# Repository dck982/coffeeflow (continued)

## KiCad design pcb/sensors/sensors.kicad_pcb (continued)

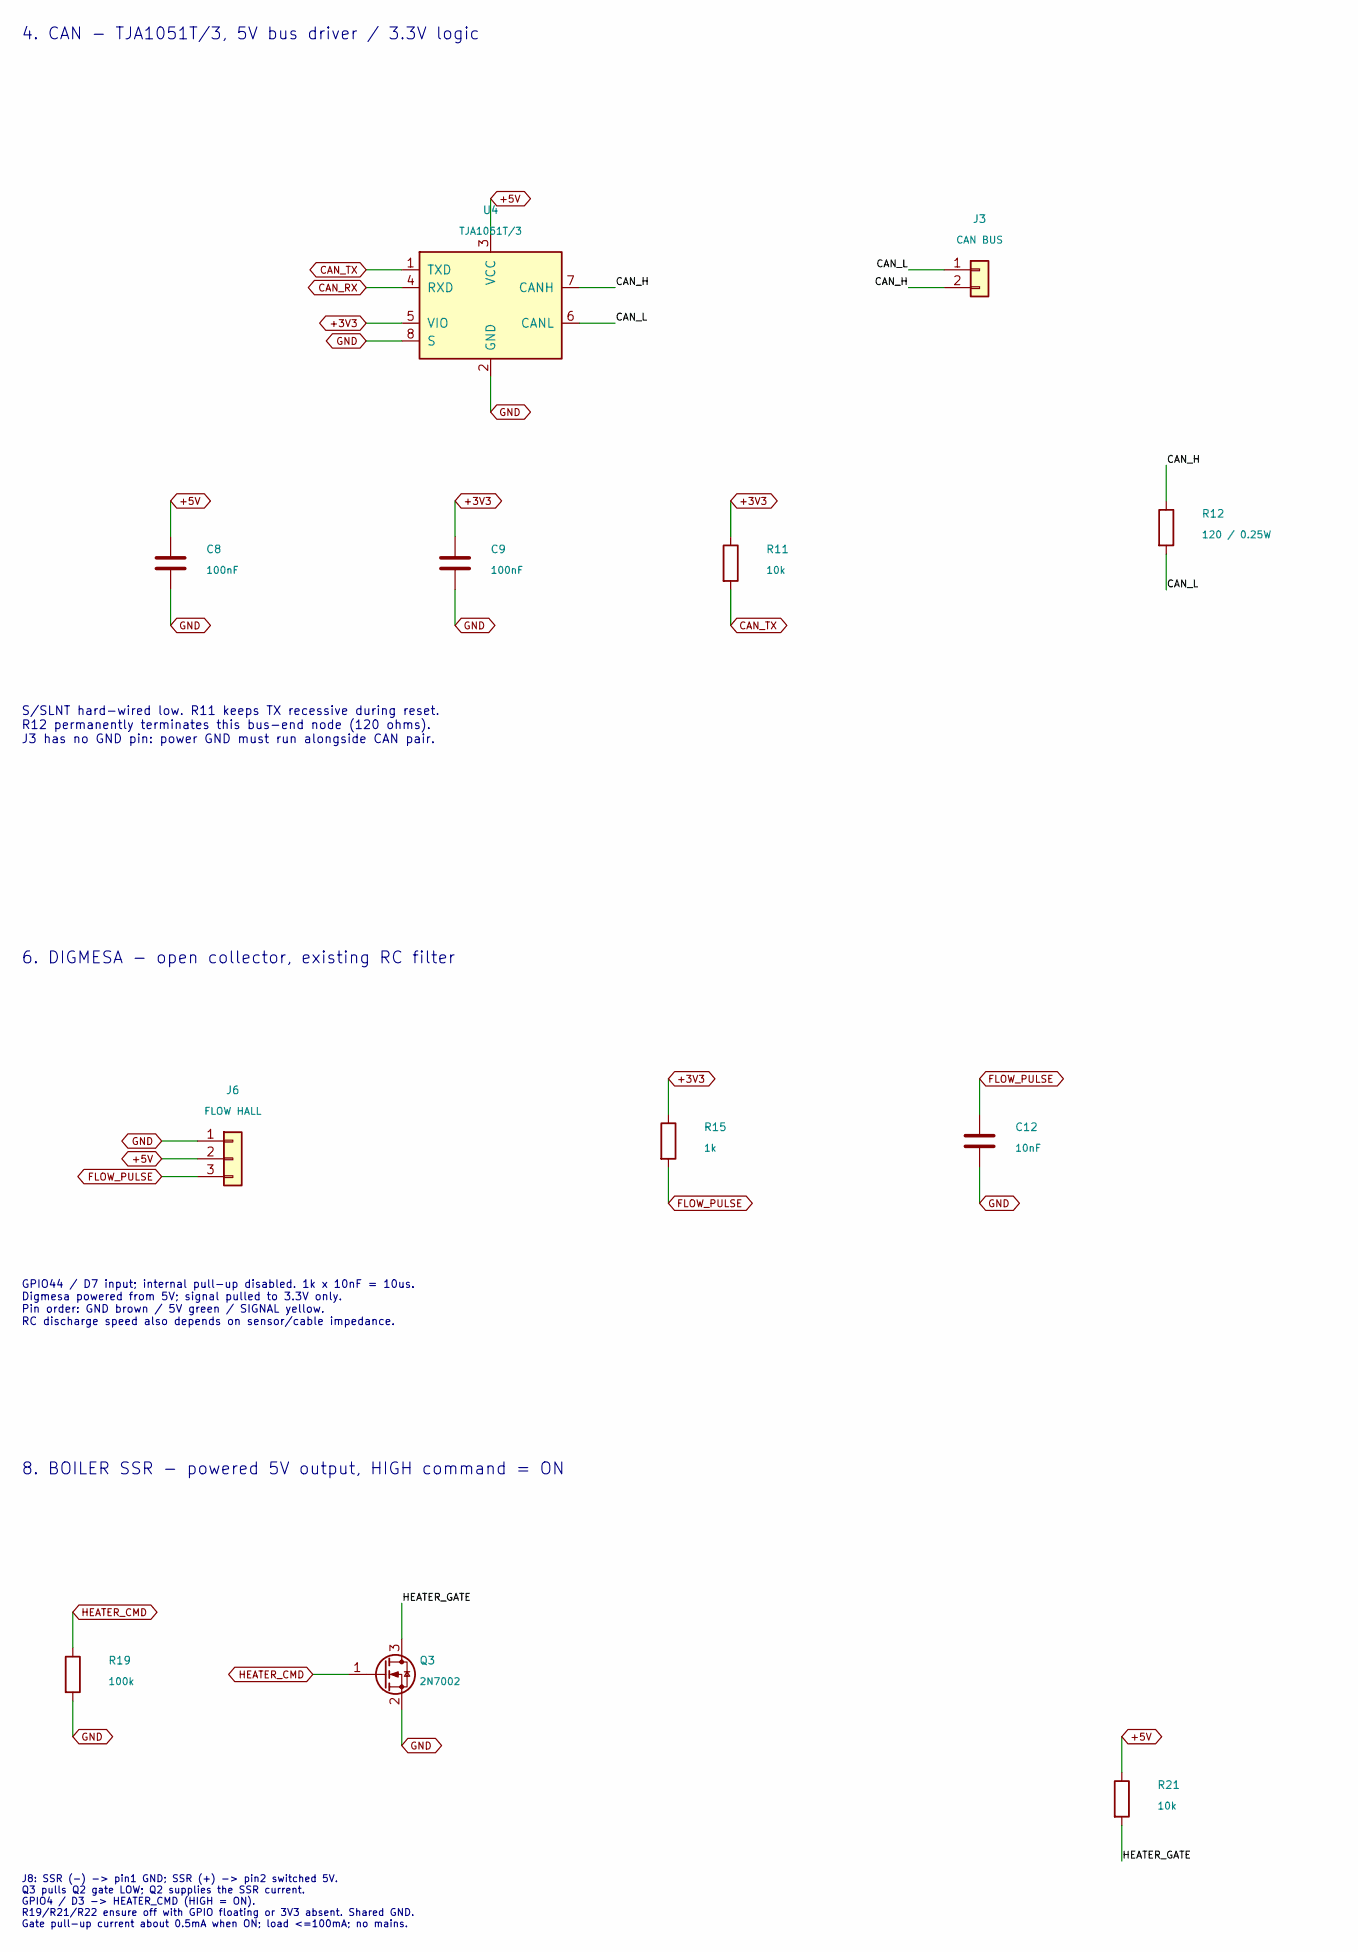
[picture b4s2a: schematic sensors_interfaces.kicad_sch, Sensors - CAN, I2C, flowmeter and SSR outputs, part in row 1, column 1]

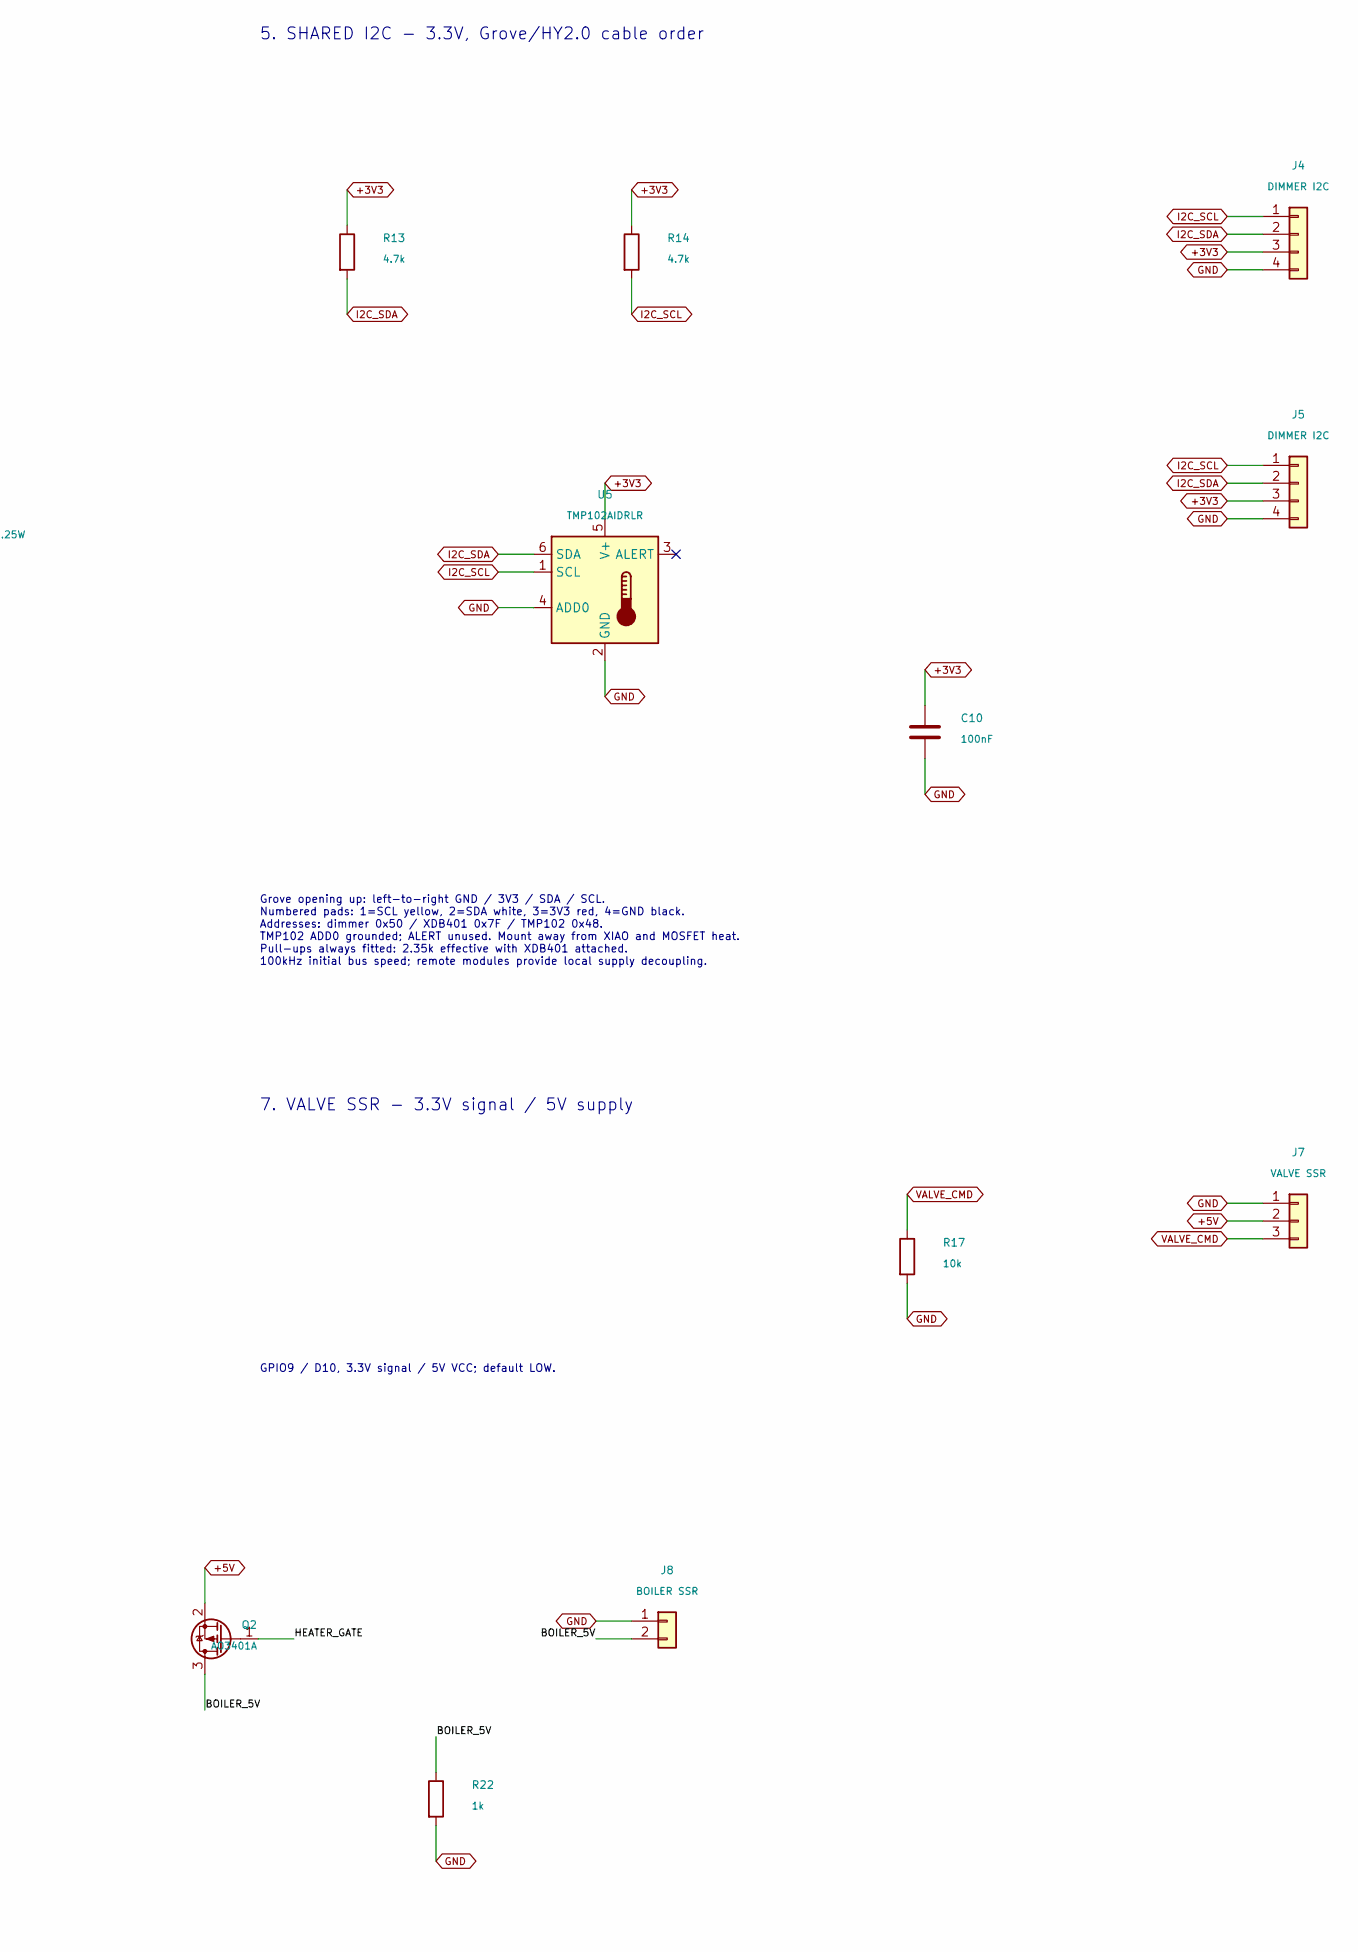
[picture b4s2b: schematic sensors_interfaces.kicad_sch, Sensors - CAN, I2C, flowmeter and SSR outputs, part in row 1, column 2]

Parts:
C8, C9, C10: 100nF; C_0603_1608Metric; MPN CC0603KRX7R9BB104; LCSC C14663
C12: 10nF; C_0603_1608Metric; MPN 0603B103K500NT; LCSC C57112
J3: CAN BUS; JST_XH_B2B-XH-A_1x02_P2.50mm_Vertical; MPN B2B-XH-A(LF)(SN); LCSC C158012
J4, J5: DIMMER I2C; CONN-TH_HY-4A; MPN HY-4A; LCSC C722737
J6: FLOW HALL; JST_XH_B3B-XH-A_1x03_P2.50mm_Vertical; MPN B3B-XH-A(LF)(SN); LCSC C144394
J7: VALVE SSR; JST_XH_B3B-XH-A_1x03_P2.50mm_Vertical; MPN B3B-XH-A(LF)(SN); LCSC C144394
J8: BOILER SSR; JST_XH_B2B-XH-A_1x02_P2.50mm_Vertical; MPN B2B-XH-A(LF)(SN); LCSC C158012
Q2: AO3401A; SOT-23; MPN AO3401A; LCSC C15127
Q3: 2N7002; SOT-23; MPN 2N7002; LCSC C8545
R11, R17, R21: 10k; R_0603_1608Metric; MPN 0603WAF1002T5E; LCSC C25804
R12: 120 / 0.25W; R_1206_3216Metric; MPN 1206W4F1200T5E; LCSC C17909
R13, R14: 4.7k; R_0603_1608Metric; MPN 0603WAF4701T5E; LCSC C23162
R15, R22: 1k; R_0603_1608Metric; MPN 0603WAF1001T5E; LCSC C21190
R19: 100k; R_0603_1608Metric; MPN 0603WAF1003T5E; LCSC C25803
U4: TJA1051T/3; SOIC-8_3.9x4.9mm_P1.27mm; MPN TJA1051T/3/1J; LCSC C38695
U5: TMP102AIDRLR; SOT-563; MPN TMP102AIDRLR; LCSC C99269

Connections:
+3V3: C9.1, C10.1, J4.3, J5.3, R11.1, R13.1, R14.1, R15.1, U4.5 (VIO), U5.5 (V+); also elsewhere on the board
+5V: C8.1, J6.2, J7.2, Q2.2 (S), R21.1, U4.3 (VCC); also elsewhere on the board
/Sensors interfaces/BOILER_5V: J8.2, Q2.3 (D), R22.1
/Sensors interfaces/CAN_H: J3.2, R12.1, U4.7 (CANH)
/Sensors interfaces/CAN_L: J3.1, R12.2, U4.6 (CANL)
/Sensors interfaces/HEATER_GATE: Q2.1 (G), Q3.3 (D), R21.2
CAN_RX: U4.4 (RXD); also elsewhere on the board
CAN_TX: R11.2, U4.1 (TXD); also elsewhere on the board
FLOW_PULSE: C12.1, J6.3, R15.2; also elsewhere on the board
GND: C8.2, C9.2, C10.2, C12.2, J4.4, J5.4, J6.1, J7.1, J8.1, Q3.2 (S), R17.2, R19.2, R22.2, U4.2 (GND), U4.8 (S), U5.2 (GND), U5.4 (ADD0); also elsewhere on the board
HEATER_CMD: Q3.1 (G), R19.1; also elsewhere on the board
I2C_SCL: J4.1, J5.1, R14.2, U5.1 (SCL); also elsewhere on the board
I2C_SDA: J4.2, J5.2, R13.2, U5.6 (SDA); also elsewhere on the board
VALVE_CMD: J7.3, R17.1; also elsewhere on the board

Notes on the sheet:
8. BOILER SSR - powered 5V output, HIGH command = ON
5. SHARED I2C - 3.3V, Grove/HY2.0 cable order
4. CAN - TJA1051T/3, 5V bus driver / 3.3V logic
6. DIGMESA - open collector, existing RC filter
Grove opening up: left-to-right GND / 3V3 / SDA / SCL. Numbered pads: 1=SCL yellow, 2=SDA white, 3=3V3 red, 4=GND black. Addresses: dimmer 0x50 / XDB401 0x7F / TMP102 0x48. TMP102 ADD0 grounded; ALERT unused. Mount away from XIAO and MOSFET heat. Pull-ups always fitted: 2.35k effective with XDB401 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
GPIO9 / D10, 3.3V signal / 5V VCC; default LOW.
S/SLNT hard-wired low. R11 keeps TX recessive during reset. R12 permanently terminates this bus-end node (120 ohms). J3 has no GND pin: power GND must run alongside CAN pair.
7. VALVE SSR - 3.3V signal / 5V supply
J8: SSR (-) -> pin1 GND; SSR (+) -> pin2 switched 5V. Q3 pulls Q2 gate LOW; Q2 supplies the SSR current. GPIO4 / D3 -> HEATER_CMD (HIGH = ON). R19/R21/R22 ensure off with GPIO floating or 3V3 absent. Shared GND. Gate pull-up current about 0.5mA when ON; load <=100mA; no mains.
GPIO44 / D7 input; internal pull-up disabled. 1k x 10nF = 10us. Digmesa powered from 5V; signal pulled to 3.3V only. Pin order: GND brown / 5V green / SIGNAL yellow. RC discharge speed also depends on sensor/cable impedance.

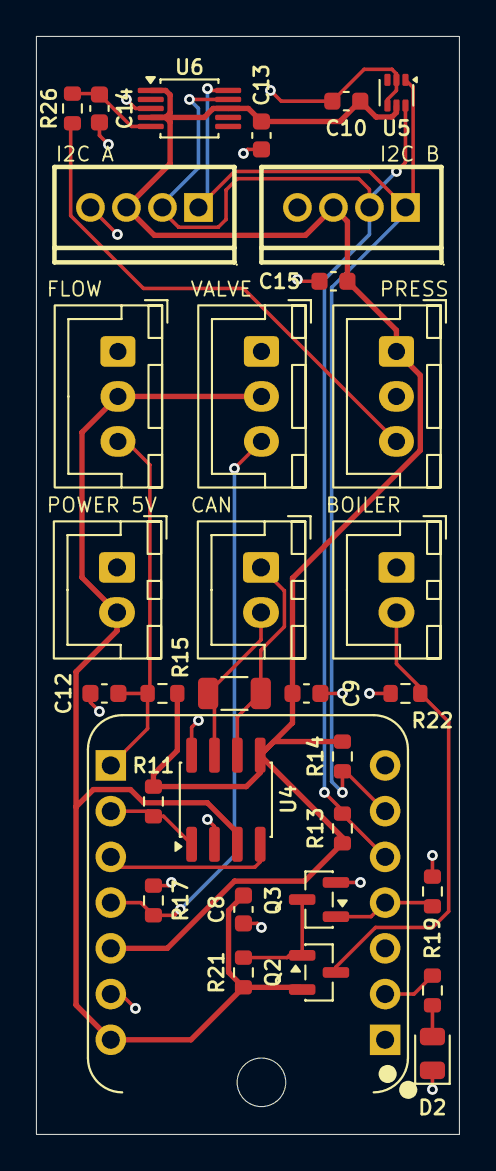
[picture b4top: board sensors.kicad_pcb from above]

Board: 2 copper layers, 23.5 x 61.0 mm, 35 parts (0 on the bottom side), 18 nets.

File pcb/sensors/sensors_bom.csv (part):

Reference,Value,Footprint,DNP,LCSC,MPN,Description,Sheet,SchematicReference,Manufacturer,JLCClass,Assembly,CheckedDate,SourceURL,Notes
C8,100nF,Capacitor_SMD:C_0603_1608Metric,False,C14663,CC0603KRX7R9BB104,Unpolarized capacitor,sensors_interfaces.kicad_sch,C8,YAGEO,Basic,SMT,2026-10-11,https://jlcpcb.com/partdetail/x/C14663,
C9,100nF,Capacitor_SMD:C_0603_1608Metric,False,C14663,CC0603KRX7R9BB104,Unpolarized capacitor,sensors_interfaces.kicad_sch,C9,YAGEO,Basic,SMT,2026-10-11,https://jlcpcb.com/partdetail/x/C14663,
C10,100nF,Capacitor_SMD:C_0603_1608Metric,False,C14663,CC0603KRX7R9BB104,Unpolarized capacitor,sensors_interfaces.kicad_sch,C10,YAGEO,Basic,SMT,2026-10-11,https://jlcpcb.com/partdetail/x/C14663,
C12,10nF,Capacitor_SMD:C_0603_1608Metric,False,C57112,0603B103K500NT,Unpolarized capacitor,sensors_interfaces.kicad_sch,C12,FH (Guangdong Fenghua Advanced Tech),Basic,SMT,2026-10-11,https://jlcpcb.com/partdetail/x/C57112,
C13,100nF,Capacitor_SMD:C_0603_1608Metric,False,C14663,CC0603KRX7R9BB104,At U6 VDD,sensors.kicad_sch,C13,YAGEO,Basic,SMT,2026-10-11,https://jlcpcb.com/partdetail/x/C14663,100nF 50V X7R 0603; U6 ADS1115 decoupling.
C14,10uF,Capacitor_SMD:C_0603_1608Metric,False,C19702,CL10A106KP8NNNC,1k/10uF fc~16Hz; X5R 10V,sensors.kicad_sch,C14,Samsung Electro-Mechanics,Basic,SMT,2026-10-11,https://jlcpcb.com/partdetail/x/C19702,10uF 10V X5R 0603; pressure input filter with R26 (16 Hz).
C15,100nF,Capacitor_SMD:C_0603_1608Metric,False,C14663,CC0603KRX7R9BB104,At J10 supply,sensors.kicad_sch,C15,YAGEO,Basic,SMT,2026-10-11,https://jlcpcb.com/partdetail/x/C14663,100nF 50V X7R 0603; decoupling at the J10 pressure sensor supply.
D2,GREEN / STATUS,LED_SMD:LED_0805_2012Metric,False,C2297,KT-0805G,"Green status LED, pin 1 cathode to GND",sensors.kicad_sch,D2,Hubei KENTO Elec,Basic,SMT,2026-10-11,https://jlcpcb.com/partdetail/x/C2297,"Emerald green 0805; pin 1 cathode to GND, pin 2 anode via R25 (1k) from GPIO2."
J1,5V POWER,Connector_JST:JST_XH_B2B-XH-A_1x02_P2.50mm_Vertical,False,C158012,B2B-XH-A(LF)(SN),"Generic connector, single row, 01x02, script generated (kicad-library-utils/schlib/autogen/connector/)",sensors.kicad_sch,J1,JST,Extended,THT,2026-10-11,https://jlcpcb.com/partdetail/x/C158012,
J3,CAN BUS,Connector_JST:JST_XH_B2B-XH-A_1x02_P2.50mm_Vertical,False,C158012,B2B-XH-A(LF)(SN),"Generic connector, single row, 01x02, script generated (kicad-library-utils/schlib/autogen/connector/)",sensors_interfaces.kicad_sch,J3,JST,Extended,THT,2026-10-11,https://jlcpcb.com/partdetail/x/C158012,
J4,DIMMER I2C,Sensors_Local:CONN-TH_HY-4A,False,C722737,HY-4A,"Generic connector, single row, 01x04, script generated (kicad-library-utils/schlib/autogen/connector/)",sensors_interfaces.kicad_sch,J4,CAX,Extended,THT,2026-10-11,https://jlcpcb.com/partdetail/x/C722737,"CAX vertical HY 4-pin, 2mm pitch; user confirmed model displays in JLCPCB. Retain NS-Tech Grove pin layout, but update PCB drills to supplier CAD 1.0mm (current drills 0.762mm). CPL uses pin-row midpoint and -90 degree rotation offset matched to supplier pad numbering."
J5,DIMMER I2C,Sensors_Local:CONN-TH_HY-4A,False,C722737,HY-4A,"Generic connector, single row, 01x04, script generated (kicad-library-utils/schlib/autogen/connector/)",sensors_interfaces.kicad_sch,J5,CAX,Extended,THT,2026-10-11,https://jlcpcb.com/partdetail/x/C722737,"Second parallel Grove I2C connector (PCB I2C A), same SCL/SDA/3V3/GND bus and C722737 sourcing as J4 (I2C B)."
J6,FLOW HALL,Connector_JST:JST_XH_B3B-XH-A_1x03_P2.50mm_Vertical,False,C144394,B3B-XH-A(LF)(SN),"Generic connector, single row, 01x03, script generated (kicad-library-utils/schlib/autogen/connector/)",sensors_interfaces.kicad_sch,J6,JST,Extended,THT,2026-10-11,https://jlcpcb.com/partdetail/x/C144394,
J7,VALVE SSR,Connector_JST:JST_XH_B3B-XH-A_1x03_P2.50mm_Vertical,False,C144394,B3B-XH-A(LF)(SN),"Generic connector, single row, 01x03, script generated (kicad-library-utils/schlib/autogen/connector/)",sensors_interfaces.kicad_sch,J7,JST,Extended,THT,2026-10-11,https://jlcpcb.com/partdetail/x/C144394,
J8,BOILER SSR,Connector_JST:JST_XH_B2B-XH-A_1x02_P2.50mm_Vertical,False,C158012,B2B-XH-A(LF)(SN),"Generic connector, single row, 01x02, script generated (kicad-library-utils/schlib/autogen/connector/)",sensors_interfaces.kicad_sch,J8,JST,Extended,THT,2026-10-11,https://jlcpcb.com/partdetail/x/C158012,
J10,PRESSURE,Connector_JST:JST_XH_B3B-XH-A_1x03_P2.50mm_Vertical,False,C144394,B3B-XH-A(LF)(SN),"Pin 1 3V3, 2 GND, 3 sensor output",sensors.kicad_sch,J10,JST,Extended,THT,2026-10-11,https://jlcpcb.com/partdetail/x/C144394,"Pressure sensor input: pin 1 3V3, 2 GND, 3 output."
J11,XIAO D0-D6,Sensors_Local:XIAO_Socket_1x07_P2.54mm_Vertical,False,C22438157,HX PM2.54-1x7P ZC-Y,Female 1x7 socket for XIAO pins 1-7 (D0-D6),sensors.kicad_sch,J11,hanxia,Extended,THT,2026-10-11,https://jlcpcb.com/partdetail/x/C22438157,"Female 1x7 2.54 mm socket, 8.5 mm high, for XIAO pins 1-7. Soldered by JLCPCB (THT); the XIAO plugs in by hand."
J12,XIAO D7-5V,Sensors_Local:XIAO_Socket_1x07_P2.54mm_Vertical,False,C22438157,HX PM2.54-1x7P ZC-Y,"Female 1x7 socket for XIAO pins 8-14 (D7-D10, 3V3, GND, 5V)",sensors.kicad_sch,J12,hanxia,Extended,THT,2026-10-11,https://jlcpcb.com/partdetail/x/C22438157,"Female 1x7 2.54 mm socket, 8.5 mm high, for XIAO pins 8-14. Soldered by JLCPCB (THT); the XIAO plugs in by hand."
Q2,AO3401A,Package_TO_SOT_SMD:SOT-23,False,C15127,AO3401A,"-4.0A Id, -30V Vds, P-Channel MOSFET, SOT-23",sensors_interfaces.kicad_sch,Q2,Alpha & Omega Semicon,Basic,SMT,2026-10-11,https://jlcpcb.com/partdetail/x/C15127,
Q3,2N7002,Package_TO_SOT_SMD:SOT-23,False,C8545,2N7002,"0.115A Id, 60V Vds, N-Channel MOSFET, SOT-23",sensors_interfaces.kicad_sch,Q3,"Jiangsu Changjing Electronics Technology Co., Ltd.",Basic,SMT,2026-10-11,https://jlcpcb.com/partdetail/x/C8545,
R11,10k,Resistor_SMD:R_0603_1608Metric,False,C25804,0603WAF1002T5E,Resistor,sensors_interfaces.kicad_sch,R11,UNI-ROYAL(Uniroyal Elec),Basic,SMT,2026-10-11,https://jlcpcb.com/partdetail/x/C25804,
R12,120 / 0.25W,Resistor_SMD:R_1206_3216Metric,False,C17909,1206W4F1200T5E,Resistor,sensors_interfaces.kicad_sch,R12,UNI-ROYAL(Uniroyal Elec),Basic,SMT,2026-10-11,https://jlcpcb.com/partdetail/x/C17909,
R13,4.7k,Resistor_SMD:R_0603_1608Metric,False,C23162,0603WAF4701T5E,Resistor,sensors_interfaces.kicad_sch,R13,UNI-ROYAL(Uniroyal Elec),Basic,SMT,2026-10-11,https://jlcpcb.com/partdetail/x/C23162,
R14,4.7k,Resistor_SMD:R_0603_1608Metric,False,C23162,0603WAF4701T5E,Resistor,sensors_interfaces.kicad_sch,R14,UNI-ROYAL(Uniroyal Elec),Basic,SMT,2026-10-11,https://jlcpcb.com/partdetail/x/C23162,
R15,1k,Resistor_SMD:R_0603_1608Metric,False,C21190,0603WAF1001T5E,Resistor,sensors_interfaces.kicad_sch,R15,UNI-ROYAL(Uniroyal Elec),Basic,SMT,2026-10-11,https://jlcpcb.com/partdetail/x/C21190,
R17,10k,Resistor_SMD:R_0603_1608Metric,False,C25804,0603WAF1002T5E,Resistor,sensors_interfaces.kicad_sch,R17,UNI-ROYAL(Uniroyal Elec),Basic,SMT,2026-10-11,https://jlcpcb.com/partdetail/x/C25804,
R19,100k,Resistor_SMD:R_0603_1608Metric,False,C25803,0603WAF1003T5E,Resistor,sensors_interfaces.kicad_sch,R19,UNI-ROYAL(Uniroyal Elec),Basic,SMT,2026-10-11,https://jlcpcb.com/partdetail/x/C25803,
R21,10k,Resistor_SMD:R_0603_1608Metric,False,C25804,0603WAF1002T5E,Resistor,sensors_interfaces.kicad_sch,R21,UNI-ROYAL(Uniroyal Elec),Basic,SMT,2026-10-11,https://jlcpcb.com/partdetail/x/C25804,
R22,1k,Resistor_SMD:R_0603_1608Metric,False,C21190,0603WAF1001T5E,Resistor,sensors_interfaces.kicad_sch,R22,UNI-ROYAL(Uniroyal Elec),Basic,SMT,2026-10-11,https://jlcpcb.com/partdetail/x/C21190,
R25,1k,Resistor_SMD:R_0603_1608Metric,False,C21190,0603WAF1001T5E,Resistor,sensors.kicad_sch,R25,UNI-ROYAL(Uniroyal Elec),Basic,SMT,2026-10-11,https://jlcpcb.com/partdetail/x/C21190,
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
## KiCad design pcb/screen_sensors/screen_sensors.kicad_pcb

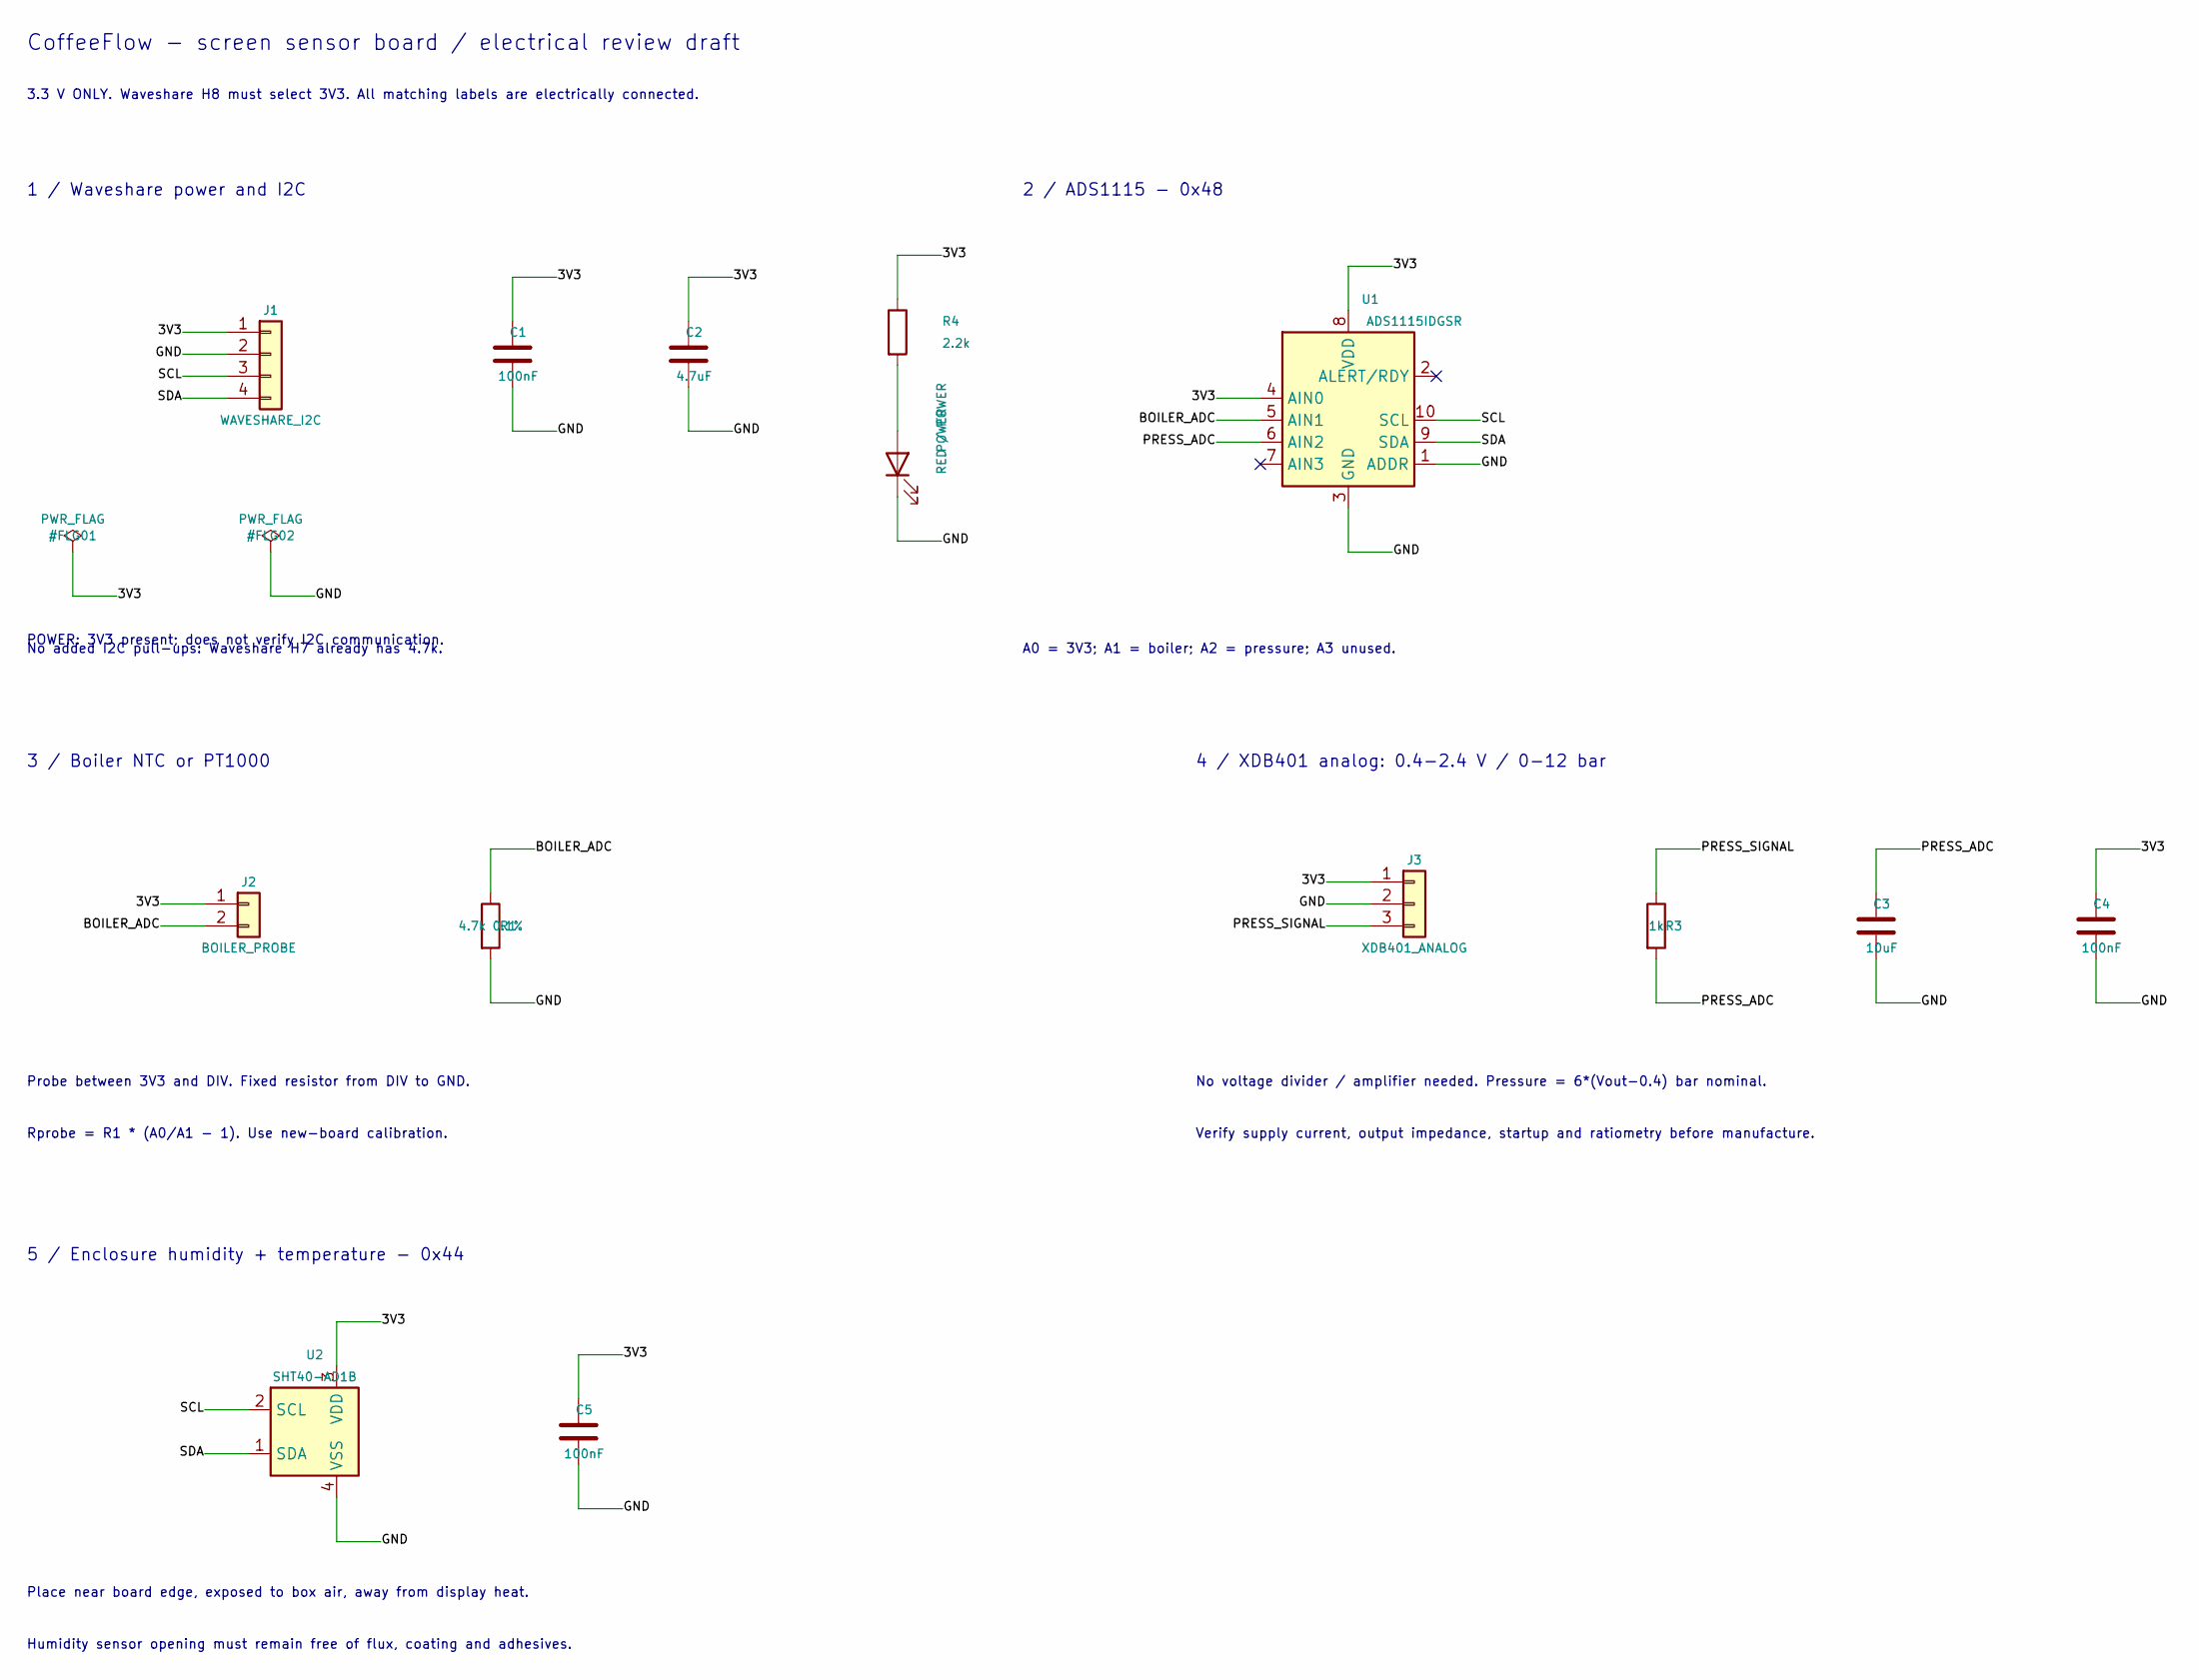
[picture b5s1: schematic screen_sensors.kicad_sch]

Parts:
C1, C4, C5: 100nF; C_0603_1608Metric; MPN CC0603KRX7R9BB104; LCSC C14663
C2: 4.7uF; C_0603_1608Metric; MPN CL10A475KO8NNNC; LCSC C19666
C3: 10uF; C_0603_1608Metric; MPN CL10A106KP8NNNC; LCSC C19702
J1: WAVESHARE_I2C; JST_XH_B4B-XH-A_1x04_P2.50mm_Vertical; MPN B4B-XH-A(LF)(SN); LCSC C144395
J2: BOILER_PROBE; JST_XH_B2B-XH-A_1x02_P2.50mm_Vertical; MPN B2B-XH-A-R(LF)(SN); LCSC C495685
J3: XDB401_ANALOG; JST_XH_B3B-XH-A_1x03_P2.50mm_Vertical; MPN B3B-XH-A(LF)(SN); LCSC C144394
POWER: RED / POWER; LED_0603_1608Metric; MPN KT-0603R; LCSC C2286
R1: 4.7k 0.1%; R_0603_1608Metric; MPN PTFR0603B4K70N9; LCSC C394547
R3: 1k; R_0603_1608Metric; MPN 0603WAF1001T5E; LCSC C21190
R4: 2.2k; R_0603_1608Metric; MPN 0603WAF2201T5E; LCSC C4190
U1: ADS1115IDGSR; TSSOP-10_3x3mm_P0.5mm; MPN ADS1115IDGSR; LCSC C37593
U2: SHT40-AD1B; Sensirion_DFN-4_1.5x1.5mm_P0.8mm_SHT4x_NoCentralPad; MPN SHT40-AD1B-R3; LCSC C2848306

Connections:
/3V3: C1.1, C2.1, C4.1, C5.1, J1.1, J2.1, J3.1, R4.1, U1.4 (AIN0), U1.8 (VDD), U2.3 (VDD)
/BOILER_ADC: J2.2, R1.1, U1.5 (AIN1)
/GND: C1.2, C2.2, C3.2, C4.2, C5.2, J1.2, J3.2, POWER.1 (K), R1.2, U1.1 (ADDR), U1.3 (GND), U2.4 (VSS)
/PRESS_ADC: C3.1, R3.2, U1.6 (AIN2)
/PRESS_SIGNAL: J3.3, R3.1
/SCL: J1.3, U1.10 (SCL), U2.2 (SCL)
/SDA: J1.4, U1.9 (SDA), U2.1 (SDA)
unnamed: POWER.2 (A), R4.2

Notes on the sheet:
CoffeeFlow - screen sensor board / electrical review draft
3.3 V ONLY. Waveshare H8 must select 3V3. All matching labels are electrically connected.
1 / Waveshare power and I2C
No added I2C pull-ups: Waveshare H7 already has 4.7k.
2 / ADS1115 - 0x48
A0 = 3V3; A1 = boiler; A2 = pressure; A3 unused.
3 / Boiler NTC or PT1000
Probe between 3V3 and DIV. Fixed resistor from DIV to GND.
Rprobe = R1 * (A0/A1 - 1). Use new-board calibration.
4 / XDB401 analog: 0.4-2.4 V / 0-12 bar
No voltage divider / amplifier needed. Pressure = 6*(Vout-0.4) bar nominal.
Verify supply current, output impedance, startup and ratiometry before manufacture.
5 / Enclosure humidity + temperature - 0x44
Place near board edge, exposed to box air, away from display heat.
Humidity sensor opening must remain free of flux, coating and adhesives.
POWER: 3V3 present; does not verify I2C communication.

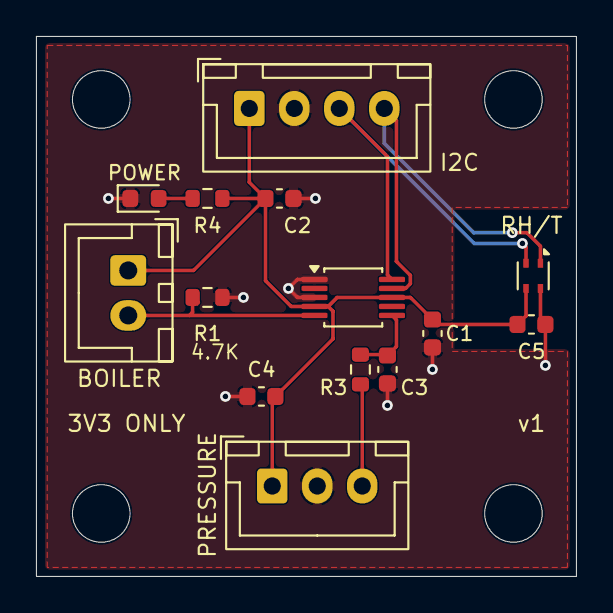
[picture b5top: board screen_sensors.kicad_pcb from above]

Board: 2 copper layers, 30.0 x 30.0 mm, 18 parts (0 on the bottom side), 8 nets.

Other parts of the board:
H1, H2, H3, H4: M3; MountingHole_3.2mm_M3

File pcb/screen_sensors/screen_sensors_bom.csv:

Reference,Value,Footprint,DNP,MPN,LCSC,Note
J1,WAVESHARE_I2C,Connector_JST:JST_XH_B4B-XH-A_1x04_P2.50mm_Vertical,False,B4B-XH-A(LF)(SN),C144395,"Pin 1 VCC/3V3, 2 GND, 3 SCL, 4 SDA; cross SDA/SCL in Waveshare cable"
C1,100nF,Capacitor_SMD:C_0603_1608Metric,False,CC0603KRX7R9BB104,C14663,At U1 VDD
C2,4.7uF,Capacitor_SMD:C_0603_1608Metric,False,CL10A475KO8NNNC,C19666,"Board bulk, X5R 16V"
U1,ADS1115IDGSR,Package_SO:TSSOP-10_3x3mm_P0.5mm,False,ADS1115IDGSR,C37593,ADDR=GND; PGA +/-4.096V; A0 measures divider supply
J2,BOILER_PROBE,Connector_JST:JST_XH_B2B-XH-A_1x02_P2.50mm_Vertical,False,B2B-XH-A-R(LF)(SN),C495685,
R1,4.7k 0.1%,Resistor_SMD:R_0603_1608Metric,False,PTFR0603B4K70N9,C394547,Precision / low TCR; calibrate new assembly
J3,XDB401_ANALOG,Connector_JST:JST_XH_B3B-XH-A_1x03_P2.50mm_Vertical,False,B3B-XH-A(LF)(SN),C144394,"Pin 1 3V3, 2 GND, 3 output; verify sensor wire colors"
R3,1k,Resistor_SMD:R_0603_1608Metric,False,0603WAF1001T5E,C21190,JLCPCB basic; 1%; provisional pressure RC filter
C3,10uF,Capacitor_SMD:C_0603_1608Metric,False,CL10A106KP8NNNC,C19702,"Input filter at ADC; 1k/10uF fc~16Hz; X5R 10V"
C4,100nF,Capacitor_SMD:C_0603_1608Metric,False,CC0603KRX7R9BB104,C14663,At pressure connector supply
U2,SHT40-AD1B,Sensor_Humidity:Sensirion_DFN-4_1.5x1.5mm_P0.8mm_SHT4x_NoCentralPad,False,SHT40-AD1B-R3,C2848306,Top-side SMT reflow with ADS1115; no board wash; address 0x44
C5,100nF,Capacitor_SMD:C_0603_1608Metric,False,CC0603KRX7R9BB104,C14663,At U2 VDD
R4,2.2k,Resistor_SMD:R_0603_1608Metric,False,0603WAF2201T5E,C4190,JLCPCB basic; 1%; power LED current limiting
POWER,RED / POWER,LED_SMD:LED_0603_1608Metric,False,KT-0603R,C2286,JLCPCB basic; red power indicator; approximately 0.6mA; pin 1 cathode to GND

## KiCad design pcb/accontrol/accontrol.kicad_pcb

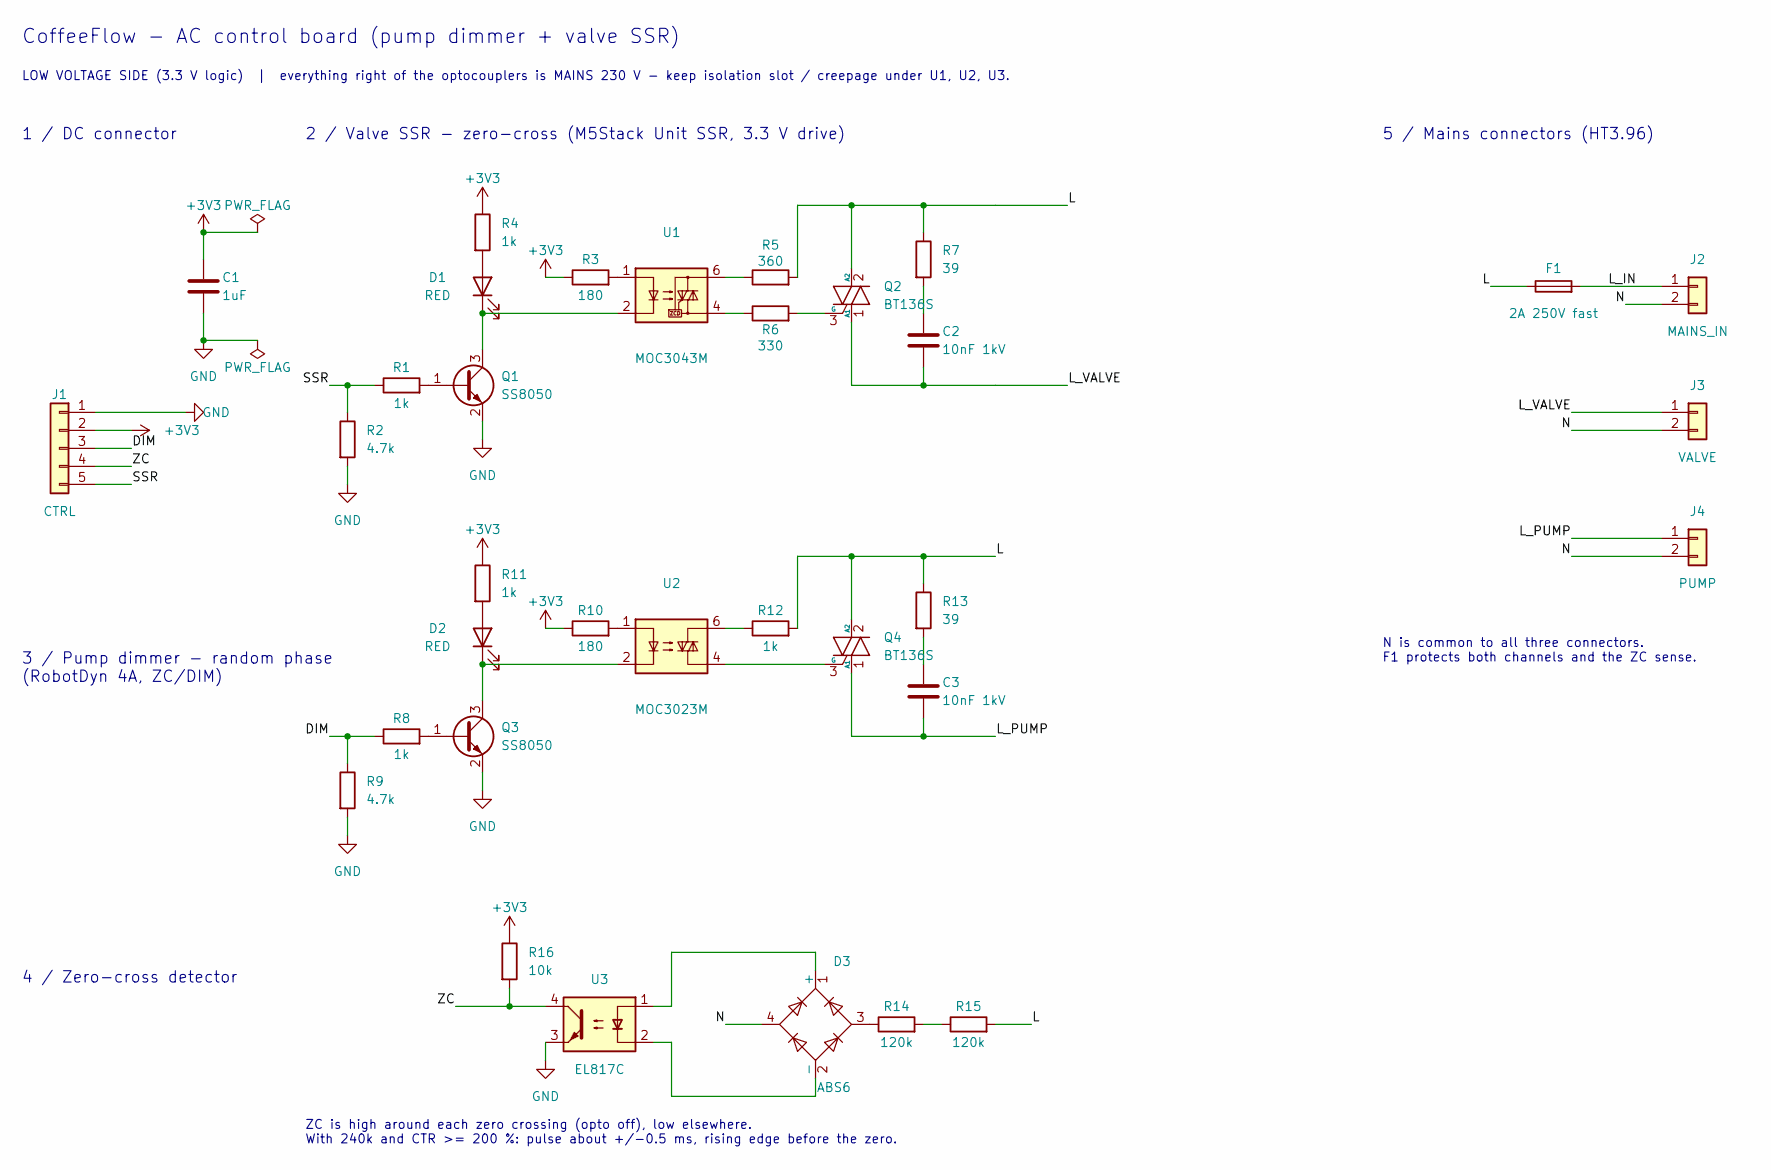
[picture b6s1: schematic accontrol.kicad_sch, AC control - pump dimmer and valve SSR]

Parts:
C1: 1uF; C_0603_1608Metric
C2, C3: 10nF 1kV; C_1206_3216Metric
D1, D2: RED; LED_0603_1608Metric
D3: ABS6; Diode_Bridge_Diotec_ABS; MPN ABS6; LCSC C48642435
F1: 2A 250V fast; F2410; MPN MF2410F2.000TM; LCSC C83797
J1: CTRL; JST_XH_B5B-XH-A_1x05_P2.50mm_Vertical; MPN B5B-XH-A(LF)(SN)
J2: MAINS_IN; CONN-TH_P3.96_HT396R-3.96-2P; MPN HT396R-3.96-2P; LCSC C577799
J3: VALVE; CONN-TH_P3.96_HT396R-3.96-2P; MPN HT396R-3.96-2P; LCSC C577799
J4: PUMP; CONN-TH_P3.96_HT396R-3.96-2P; MPN HT396R-3.96-2P; LCSC C577799
Q1, Q3: SS8050; SOT-23; MPN SS8050 (Y1)
Q2, Q4: BT136S; TO-252-2; MPN BT136S; LCSC C23427
R1, R4, R8, R11: 1k; R_0603_1608Metric
R2, R9: 4.7k; R_0603_1608Metric
R3, R10: 180; R_0603_1608Metric
R5: 360; R_1206_3216Metric
R6: 330; R_1206_3216Metric
R7: 39; R_1206_3216Metric
R12: 1k; R_1206_3216Metric
R13: 39; R_1210_3225Metric; MPN RC1210JR-0739RL; LCSC C728404
R14, R15: 120k; R_1210_3225Metric; MPN 1210W2F1203T5E; LCSC C422421
R16: 10k; R_0603_1608Metric
U1: MOC3043M; SMDIP-6_W9.53mm_Slot; MPN MOC3043M
U2: MOC3023M; SMDIP-6_W9.53mm_Slot; MPN MOC3023M
U3: EL817C; SMDIP-4_W9.53mm_Slot; MPN EL817S1(C)(TU)-F

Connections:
+3V3: C1.1, J1.2, R3.1, R4.1, R10.1, R11.1, R16.1
/DIM: J1.3, R8.1, R9.1
/L: F1.1, Q2.2 (A2), Q4.2 (A2), R5.2, R7.1, R12.2, R13.1, R15.2
/L_IN: F1.2, J2.1
/L_PUMP: C3.2, J4.1, Q4.1 (A1)
/L_VALVE: C2.2, J3.1, Q2.1 (A1)
/N: D3.4, J2.2, J3.2, J4.2
/SSR: J1.5, R1.1, R2.1
/ZC: J1.4, R16.2, U3.4
GND: C1.2, J1.1, Q1.2 (E), Q3.2 (E), R2.2, R9.2, U3.3
unnamed: C2.1, R7.2
unnamed: C3.1, R13.2
unnamed: D1.2 (A), R4.2
unnamed: D1.1 (K), Q1.3 (C), U1.2
unnamed: D2.2 (A), R11.2
unnamed: D2.1 (K), Q3.3 (C), U2.2
unnamed: D3.1 (+), U3.1
unnamed: D3.2 (-), U3.2
unnamed: D3.3, R14.1
unnamed: Q1.1 (B), R1.2
unnamed: Q2.3 (G), R6.2
unnamed: Q3.1 (B), R8.2
unnamed: Q4.3 (G), U2.4
unnamed: R3.2, U1.1
unnamed: R5.1, U1.6
unnamed: R6.1, U1.4
unnamed: R10.2, U2.1
unnamed: R12.1, U2.6
unnamed: R14.2, R15.1

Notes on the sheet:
CoffeeFlow - AC control board (pump dimmer + valve SSR)
LOW VOLTAGE SIDE (3.3 V logic) | everything right of the optocouplers is MAINS 230 V - keep isolation slot / creepage under U1, U2, U3.
1 / DC connector
2 / Valve SSR - zero-cross (M5Stack Unit SSR, 3.3 V drive)
3 / Pump dimmer - random phase (RobotDyn 4A, ZC/DIM)
4 / Zero-cross detector
5 / Mains connectors (HT3.96)
ZC is high around each zero crossing (opto off), low elsewhere. With 240k and CTR >= 200 %: pulse about +/-0.5 ms, rising edge before the zero.
N is common to all three connectors. F1 protects both channels and the ZC sense.
